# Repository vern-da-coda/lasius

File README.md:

# Lasius Hexapod

---

[Index](README.md) | [Software](software/README.md) | [Hardware](hardware/README.md) | [Docs](docs/README.md) | [Data](data/README.md) | [Scripts](scripts/README.md) |<br>
[Architecture](#folder-architecture) | [Subsystems](#core-subsystems--capabilities) | [Documentation Index](#documentation-index--navigation) | [Quickstart](#quickstart) |

---

<p align="left">

</p>
<p align="left">

</p>

Modular control software, rigid-body physics simulation, 3D Digital Twin, REST/WebSocket teleoperation daemon, and CAD engineering pipeline for an 18-DOF, 6-legged (hexapod) biomimetic walking robot.

**Interactive Web Demo:** [**https://dashboard.lasius.kaemmereit.de/**](https://dashboard.lasius.kaemmereit.de/) – Experience the browser-based 3D Digital Twin and gait engine live.

Lasius combines embedded locomotion control, 3D physics simulation (PyBullet & MuJoCo), Gymnasium Reinforcement Learning, real-time WebGL visualization, physical CAD engineering, and gamepad teleoperation into a single unified monorepo. The physical robot features a dual carbon-fiber sandwich chassis, 18 high-torque metal-gear servos driven by dual PCA9685 PWM controllers, closed-form 3-DOF inverse kinematics, a smooth 50 Hz harmonic cosine walking engine, and an interactive Digital Twin built with Vue 3 and Three.js.

---

## Core Subsystems & Capabilities

### 1. Embedded Locomotion Engine (`software/lasius-core`)
- **50 Hz Harmonic OmniGait Engine:** $C^1$-continuous trajectory generator with smooth cosine stance/swing transitions, $>5\times$ acceleration jerk reduction, and seamless morphing between **Tripod**, **Ripple**, and **Wave** gaits.
- **Analytical 3-DOF Inverse Kinematics:** Closed-form solver computing joint angles $(\theta_{\text{coxa}}, \theta_{\text{femur}}, \theta_{\text{tibia}})$ from foot Cartesian coordinates $(x, y, z)$.
- **Dynamic 6-DOF Body Attitude:** Real-time adjustment of ground clearance ($z \in [-130, -40]\,\text{mm}$), chassis roll, and pitch without altering foot ground contact.
- **REST & WebSocket API:** OpenAPI 3.1 specification serving high-level locomotion orders (`set_velocity`, `set_gait`, `reset_pose`), 25 Hz joint angle telemetry, and 10 Hz system KPIs.

### 2. 3D Physics Digital Twin & Reinforcement Learning (`scripts/sim/`)
- **Physics Simulation (PyBullet & MuJoCo):** 240 Hz rigid-body simulation with Coulomb ground friction ($\mu = 1.2$), accurate joint limits, and stable insect stance with elevated femur and 90° tibia horn offset.
- **Automated FreeCAD $\to$ URDF Pipeline:** `scripts/sim/extract_inertias.py` analytically computes masses and 3D inertia tensors directly from CAD solid models; `scripts/sim/export_urdf.py` generates [`hardware/mechanics/export/urdf/lasius.urdf`](hardware/mechanics/export/urdf/lasius.urdf).
- **Gymnasium Environment (`LasiusGymEnv`):** Standardized RL interface with 66-dimensional observation space (projected gravity vector, linear/angular velocities, joint errors, action history) and 18-dimensional continuous action space (Residual RL).
- **PPO Policy Training:** Stable-Baselines3 training pipeline (`scripts/sim/train_rl.py`) running at $>420\,\text{FPS}$ on laptop CPUs for residual gait adaptation.

### 3. 3D Web Dashboard (`software/lasius-dashboard`)
- **Vue 3 + TypeScript Single-Page App:** Reactive dashboard with Three.js WebGL 3D Digital Twin, 2D orthographic CAD projections, and real-time state telemetry.
- **Leg Control & Calibration:** Interactive joint inspection (`JointCard.vue`) supporting individual servo angle sliders, 0° reference alignment, automated collision sweeps, and live microsecond trim overlay persistence.
- **Ground Coupling:** Dynamic support plane calculation (`fitSupportPlane`) supporting *Ground Locked* (moving floor grid) and *Test Stand* (bench isolation) modes with active foot contact glow indicators.
- **Standalone Client Simulation:** Runs in browser without robot connection via an additive TypeScript kinematics engine ([`dashboard.lasius.kaemmereit.de`](https://dashboard.lasius.kaemmereit.de/)).

### 4. Gamepad Teleoperation (`software/lasius-pilot`)
- **Multi-Controller Support:** Native Linux joystick driver (`/dev/input/js0`) with auto-detecting YAML profiles for **Sony PS5 DualSense**, **Google Stadia**, and **Xbox** controllers.
- **Unified Orchestration (`scripts/sim/sim_pilot.sh`):** Concurrent startup of PyBullet 3D simulation, HTTP Web Dashboard, WebSocket bridge, and `lasius-pilot` teleoperation with graceful single-signal shutdown.

### 5. I2C Sensor Bus & Testbench (`hardware/electronics/`, `scripts/bench/`)
- **Two-Tier I2C & Logic Architecture:** Dual **Controllers** (`PCA9685` `0x40` left, `0x42` right) daisy-chained with the central **Multiplexer** (`PCA9548A` at `0x71`, avoiding `0x70 ALLCALL`), isolated per-leg **Wandler** ADCs (`6× ADS1115 V280` at `0x48` on `CH0–CH5`, verified `SCL`-before-`SDA` pinout and effective 12-bit / `2.0 mV` steps) reading servo potentiometers & Omron D2F-L foot switches (`A3`), plus a central `3.3V / GND` distribution rail tied once to `Star_Ground_Bus`.
- **Automated Diagnostic Tool (`scripts/bench/test_electronics.py`):** Full topology scan, sub-channel switching, and live analog voltage monitor with offline `--mock` mode.

---

## Folder Architecture

The repository is organized into focused subdomains:

```text
lasius/
├── software/            # Monorepo software packages
│   ├── lasius-core/     # Locomotion engine, HAL, Gymnasium environment & REST/WS daemon
│   ├── lasius-dashboard/# Vue 3 + TypeScript + Three.js 3D Digital Twin & browser GUI
│   └── lasius-pilot/    # Gamepad teleoperation client & Linux joystick driver
├── hardware/            # Physical robot engineering
│   ├── mechanics/       # Parametric FreeCAD models, STL/STEP exports & 1:1 drill templates
│   └── electronics/     # Sensor bus topology, WireViz harness diagrams & BOMs
├── docs/                # Architecture specifications, hardware plans & roadmap
├── data/                # Calibration snapshots, benchmarks & telemetry logs
└── scripts/             # Development, simulation, bench diagnostics & deployment tools
```

---

## Documentation Index & Navigation

Direct links to all distributed technical documentation, specifications, hardware plans, and subsystem guides:

### System & Architecture (`docs/`)
- [**`docs/README.md`**](docs/README.md) – Documentation overview and navigation guide
- [**`docs/domain_architecture.md`**](docs/domain_architecture.md) – Comprehensive system & domain architecture specification (6 Domains, C4 map & sequence workflows)
- [**`docs/roadmap.md`**](docs/roadmap.md) – Project roadmap, milestone progress (M1–M6), and backlog
- [**`docs/audio_briefing_domain.md`**](docs/audio_briefing_domain.md) – Audio podcast briefing script covering mechanics, kinematics, and software architecture

### Hardware & Electronics (`docs/hardware/`, `hardware/`)
- [**`docs/hardware/testbench_bringup_status.md`**](docs/hardware/testbench_bringup_status.md) – **Active Focus:** Step-by-step Bring-Up status and handover for TCA9548A & ADS1115 ADCs
- [**`docs/hardware/electronics_testbench_guide.md`**](docs/hardware/electronics_testbench_guide.md) – Technical reference guide, wiring pinouts, 3.3V logic rules, and I2C address conflict protection
- [**`docs/hardware/decisions.md`**](docs/hardware/decisions.md) – Hardware decisions, power architecture (LiPo/UBEC), sensor bus & PETG 3D print specifications
- [**`docs/hardware/closed_loop_plan.md`**](docs/hardware/closed_loop_plan.md) – 18-DOF closed-loop feedback plan, ADS1115 ADC pinout & CircuitPython drivers
- [**`docs/hardware/wiring_plan.md`**](docs/hardware/wiring_plan.md) – Raspberry Pi to PCA9685 I2C daisy chain, logic levels & common ground scheme
- [**`hardware/README.md`**](hardware/README.md) – Hardware overview, dual-plate chassis dimensions, limb lengths & power distribution
- [**`hardware/mechanics/README.md`**](hardware/mechanics/README.md) – FreeCAD parametric models, fabrication exports (STEP, STL, DXF) & SVG drill templates
- [**`hardware/mechanics/STYLE_GUIDE.md`**](hardware/mechanics/STYLE_GUIDE.md) – Mechanical & Hardware Style-Guide (Bionic design DNA, truss standards, DfAM for PETG & COTS interfaces)
- [**`hardware/electronics/wiring/README.md`**](hardware/electronics/wiring/README.md) – WireViz cable harnesses (`.yml`), visual harness diagrams, master color scheme & automated BOMs
- [**`hardware/electronics/TODO.md`**](hardware/electronics/TODO.md) – Electronics bench verification status, master color scheme, `3.3V/GND` rail & wiring backlog

### Teleoperation & Controls (`docs/pilot/`)
- [**`docs/pilot/gamepad_stadia.md`**](docs/pilot/gamepad_stadia.md) – Google Stadia Bluetooth/USB controller profile, button mappings & teleoperation

### Software Subsystems (`software/`)
- [**`software/README.md`**](software/README.md) – Software architecture overview and package guide
- [**`software/TODO.md`**](software/TODO.md) – Biomimetic backlog, Walknet ganglia architecture, and active sprint tasks
- [**`software/lasius-core/README.md`**](software/lasius-core/README.md) – Locomotion engine, 50 Hz harmonic gait, 3-DOF IK, HAL, and REST/WebSocket API
- [**`software/lasius-dashboard/README.md`**](software/lasius-dashboard/README.md) – Vue 3 + TypeScript 3D Digital Twin (Three.js WebGL), 2D projections & control GUI
- [**`software/lasius-pilot/README.md`**](software/lasius-pilot/README.md) – Direct Linux joystick driver (`/dev/input/js0`), radial deadzones & teleoperation streaming

### Data, Benchmarks & Tooling (`data/`, `scripts/`)
- [**`data/README.md`**](data/README.md) – Runtime data index, calibration snapshots & benchmark measurements
- [**`data/bench/README.md`**](data/bench/README.md) – Potentiometer sweep calibration data, linear regression parameters & validation results
- [**`scripts/README.md`**](scripts/README.md) – Complete guide to automation, simulation, testing, diagnostic, and deployment scripts

---

## Quickstart

### 1. Installation & Dependencies

```bash
# Set up Python environment and packages in editable mode:
uv sync --extra dev
# or: pip install -e software/lasius-core -e software/lasius-pilot

# Install frontend dependencies and build dashboard:
cd software/lasius-dashboard && npm install && npm run build && cd ../..
```

### 2. Run Automated Test Suite

```bash
./scripts/dev/run_tests.sh
```
*Executes all 66 automated unit and integration tests across `lasius-core` (HAL, kinematics, gait, GymEnv, orders) and `lasius-pilot`.*

### 3. Interactive 3D Physics Simulation & Gamepad Teleoperation

Launch PyBullet rigid-body physics, the 3D Web Dashboard, and Gamepad teleoperation (PS5 DualSense / Stadia / Xbox) concurrently:

```bash
./scripts/sim/sim_pilot.sh
```

Or start the standalone PyBullet 3D simulation directly:
```bash
python3 scripts/sim/run_simulation.py --gui
```

### 4. Local Simulation Server & Web Digital Twin

```bash
./scripts/dev/dev_sim.sh
```

Open your browser at:
- **3D Dashboard & Control GUI:** `http://127.0.0.1:8000`
- **Interactive OpenAPI Specification:** `http://127.0.0.1:8000/api/v1/openapi.yaml`
- **Telemetry WebSocket:** `ws://127.0.0.1:8765`

### 5. Electronics Testbench Diagnostics

Test I2C connectivity and the TCA9548A / ADS1115 sensor bus:

```bash
# On physical Raspberry Pi:
python3 scripts/bench/test_electronics.py --scan

# Offline dry-run on development workstation:
python3 scripts/bench/test_electronics.py --scan --mock
```

### 6. Deploy to Physical Raspberry Pi 4

```bash
./scripts/deploy/deploy_pi.sh [PI_IP]
```

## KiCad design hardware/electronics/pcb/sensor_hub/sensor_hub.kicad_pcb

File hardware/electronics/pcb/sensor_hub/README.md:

# Lasius Sensor Hub & 3.3V / GND Distribution Carrier Board v2

---

[Project Index](../../../../README.md) | [Electronics Roadmap](../../TODO.md) | [Wiring Plan](../../../../docs/hardware/wiring_plan.md) |<br>
[Wiring Harness Spec](../../WIRING_HARNESS_SPEC.md) | [Chassis Core Assembly](../../../mechanics/models/custom/v2/chassis_core_assembly.FCStd)

---

Dieses KiCad-Projekt umfasst das vollständige Design, den Bestückungsplan und die fertigen Fertigungsdaten (Gerber RS-274X + Excellon Drill) für das zentrale Sensor- und Power-Carrier-Board des **Lasius** Hexapods.

Die Platine sitzt auf den integrierten M2.5-Domen des Zwischenbodens ($Z = 28{,}00\,\text{mm}$) im $24\,\text{mm}$-Spalt zwischen den beiden PCA9685 PWM-Controllern und ist **zu 100 % form- und maßkompatibel zum FreeCAD-Volumenmodell** ([`sensor_hub_board.FCStd`](../../../mechanics/models/custom/v2/parts/chassis/sensor_hub_board.FCStd)).

---

## 1. Board-Spezifikationen

| Parameter | Wert | Beschreibung |
| :--- | :--- | :--- |
| **Abmessungen** | $54{,}0 \times 22{,}0 \times 1{,}60\,\text{mm}$ | Passgenau für den Zwischenboden-Schacht; $R = 2{,}0\,\text{mm}$ Eckenradien. |
| **Lagen** | 2 Lagen (Top + Bottom) | Standard FR4, $35\,\mu\text{m}$ Cu ($1\,\text{oz}$), Matt-Schwarz oder Waldgrün. |
| **Befestigung** | 2× M2.5 Bohrungen | $\varnothing 2{,}7\,\text{mm}$ im Abstand von $26{,}0\,\text{mm}$ ($X = 0{,}0, Y = \pm 13{,}0\,\text{mm}$). |
| **Multiplexer-Sockel** | 2× 12-Pin Buchsenleiste | $2{,}54\,\text{mm}$ Raster, $17{,}54\,\text{mm}$ Reihenabstand für TCA9548A / PW548A. |
| **Adresse** | **`0x71`** (Hardware-Fixed) | `A0` fest auf `3,3 V` verdrahtet; `A1` und `A2` auf `GND`. |
| **Bein-Steckplätze** | 6× 4-Pin Stiftleisten | $2{,}54\,\text{mm}$ THT (oder JST-XH), straight $1:1$ Pinout passend zu V280 ADC. |

---

## 2. Pinbelegung der 4-Pin Bein-Steckplätze

Das Pinout ist **exakt 1:1 identisch zur Reihenfolge auf den ADS1115 (`V280`) Platinen im Femur**, sodass handelsübliche 4-adrige Flachbandleitungen ohne gekreuzte Adern verwendet werden können:

| Pin | Signal | Drahtfarbe ([Master-Farbschema](../../WIRING_HARNESS_SPEC.md)) | Beschreibung |
| :---: | :--- | :--- | :--- |
| **1** | **`3,3 V`** | **Rot** | Geregelte Logikspannung vom Pi 4 (Pin 1) |
| **2** | **`GND`** | **Schwarz** | Star-GND Referenzmasse |
| **3** | **`SCx`** | **Gelb** | Multiplexer I²C-Takt (`SCL`) für Kanal $x$ |
| **4** | **`SDx`** | **Kanal-Farbe** | Multiplexer I²C-Daten (`SDA`) für Kanal $x$ |

### Kanal-Zuordnung & Kabelfarben:
* **Bank 1 ($+Y$, zeigt nach links):**
  * `J_LF` (CH0): Blau (`SD0`) + Gelb (`SC0`) $\rightarrow$ Bein Vorne Links (LF)
  * `J_LM` (CH1): Grün (`SD1`) + Gelb (`SC1`) $\rightarrow$ Bein Mitte Links (LM)
  * `J_LR` (CH2): Violett (`SD2`) + Gelb (`SC2`) $\rightarrow$ Bein Hinten Links (LR)
  * `J_RPI` (Main Bus): Blau (`SDA`) + Gelb (`SCL`) $\rightarrow$ Haupteingang vom Raspberry Pi
  * `J_PCA_L`: 2-Pin Versorgungsabgang (`3,3V / GND`) zum linken PCA9685-Controller
* **Bank 2 ($-Y$, zeigt nach rechts):**
  * `J_FR` (CH3): Orange (`SD3`) + Gelb (`SC3`) $\rightarrow$ Bein Vorne Rechts (FR)
  * `J_RM` (CH4): Weiß (`SD4`) + Gelb (`SC4`) $\rightarrow$ Bein Mitte Rechts (RM)
  * `J_RR` (CH5): Grau (`SD5`) + Gelb (`SC5`) $\rightarrow$ Bein Hinten Rechts (RR)
  * `J_AUX`: 4-Pin Erweiterung für CH6 (INA228 Stromsensor, Braun) und CH7 (ToF)
  * `J_PCA_R`: 2-Pin Versorgungsabgang (`3,3V / GND`) zum rechten PCA9685-Controller

---

## 3. Stückliste (Bill of Materials / BOM)

| Ref | Bauteil | Gehäuse / Raster | Spezifikation / Notiz |
| :--- | :--- | :--- | :--- |
| **U1** | TCA9548A / PW548A | Breakout-Modul | 8-Kanal I²C Multiplexer Modul (violett) |
| **J_TCA_L, J_TCA_R** | 2× 12-Pin Buchsenleiste | $2{,}54\,\text{mm}$ THT, 1-reihig | Bauhöhe $4{,}0\dots 8{,}5\,\text{mm}$ zum werkzeuglosen Stecken |
| **J_LF, J_LM, J_LR** | 3× 4-Pin Stiftleiste | $2{,}54\,\text{mm}$ THT (oder JST-XH) | Linke Beinbank ($+Y$) |
| **J_FR, J_RM, J_RR** | 3× 4-Pin Stiftleiste | $2{,}54\,\text{mm}$ THT (oder JST-XH) | Rechte Beinbank ($-Y$) |
| **J_RPI, J_AUX** | 2× 4-Pin Stiftleiste | $2{,}54\,\text{mm}$ THT | Pi Haupteingang & Sensor-Erweiterung |
| **J_PCA_L, J_PCA_R** | 2× 2-Pin Stiftleiste | $2{,}54\,\text{mm}$ THT | Controller Logik-Versorgung |
| **C1** | $10\,\mu\text{F}$ Elko / Tantal | Radial $D = 5{,}0\,\text{mm}$, RM $2{,}5\,\text{mm}$ | $\ge 6{,}3\,\text{V}$ Entkopplung auf der 3,3V-Schiene |
| **C2** | $100\,\text{nF}$ Keramikkondensator | Disc / MLCC RM $2{,}5\,\text{mm}$ | Hochfrequenz-Entstörung nah am Multiplexer |
| **H1, H2** | 2× M2.5 Schrauben | Zylinderkopf / Linsenkopf | Befestigung in den Monocoque-Domen ($L = 6\dots 8\,\text{mm}$) |

---

## 4. Fertigung & Bestellung (Ready-to-Order)

Die produktionsfertigen Gerber-Daten liegen gepackt bereit unter:  
**[`sensor_hub_gerbers.zip`](sensor_hub_gerbers.zip)**

### Bestellung bei JLCPCB:
1. `sensor_hub_gerbers.zip` per Drag & Drop auf [jlcpcb.com](https://jlcpcb.com) hochladen.
2. Abmessungen werden automatisch erkannt: **$54 \times 22\,\text{mm}$**, 2 Lagen.
3. PCB Color nach Wunsch wählen (Empfehlung: **Matte Black** passend zum Anthrazit PA-CF Chassis).
4. Fertigungskosten: ca. **2 $ für 5 Stück**.

### Bestellung bei AISLER:
1. `sensor_hub_gerbers.zip` (oder direkt die `.kicad_pcb`-Datei) auf [aisler.net](https://aisler.net) hochladen.
2. „Beautiful PCBs“ auswählen (Lieferzeit: **3–4 Werktage** aus Deutschland/Niederlande).

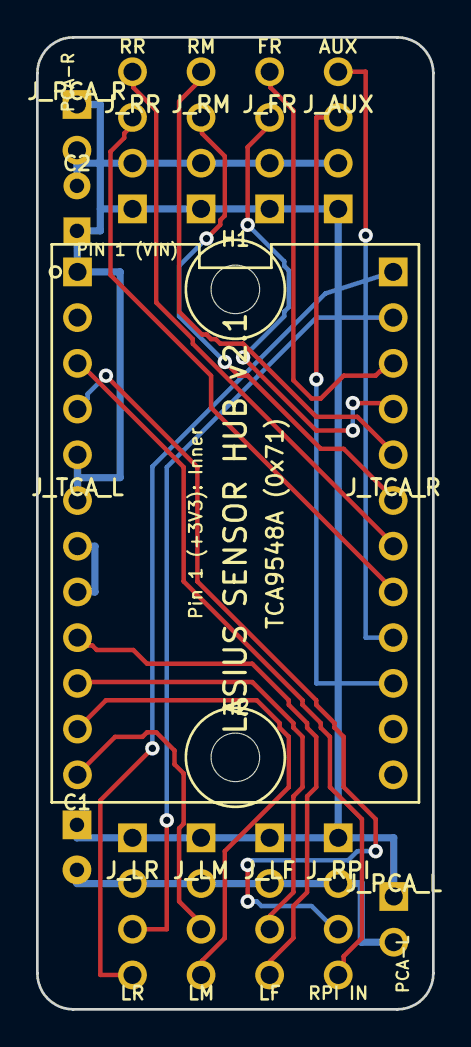
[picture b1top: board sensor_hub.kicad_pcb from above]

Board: 2 copper layers, 22.0 x 54.0 mm, 16 parts (0 on the bottom side), 18 nets.

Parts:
C1: 10uF; CP_Radial_D5.0mm_P2.50mm
C2: 100nF; C_Disc_D4.7mm_W2.6mm_P2.50mm
H1, H2: MountingHole_M2.5; MountingHole_2.7mm_M2.5
J_AUX: AUX_Sensors_CH6; PinHeader_1x04_P2.54mm_Vertical
J_FR: Right_Front_CH3; PinHeader_1x04_P2.54mm_Vertical
J_LF: Left_Front_CH0; PinHeader_1x04_P2.54mm_Vertical
J_LM: Left_Middle_CH1; PinHeader_1x04_P2.54mm_Vertical
J_LR: Left_Rear_CH2; PinHeader_1x04_P2.54mm_Vertical
J_PCA_L: PCA9685_Left_PWR; PinHeader_1x02_P2.54mm_Vertical
J_PCA_R: PCA9685_Right_PWR; PinHeader_1x02_P2.54mm_Vertical
J_RM: Right_Middle_CH4; PinHeader_1x04_P2.54mm_Vertical
J_RPI: Pi_Main_I2C_In; PinHeader_1x04_P2.54mm_Vertical
J_RR: Right_Rear_CH5; PinHeader_1x04_P2.54mm_Vertical
J_TCA_L: TCA9548A_Socket_Left; PinHeader_1x12_P2.54mm_Vertical
J_TCA_R: TCA9548A_Socket_Right; PinHeader_1x12_P2.54mm_Vertical

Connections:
+3V3: C1.1, C2.1, J_AUX.1, J_FR.1, J_LF.1, J_LM.1, J_LR.1, J_PCA_L.1, J_PCA_R.1, J_RM.1, J_RPI.1, J_RR.1, J_TCA_L.1, J_TCA_L.5, J_TCA_L.6
GND: C1.2, C2.2, J_AUX.2, J_FR.2, J_LF.2, J_LM.2, J_LR.2, J_PCA_L.2, J_PCA_R.2, J_RM.2, J_RPI.2, J_RR.2, J_TCA_L.2, J_TCA_L.7, J_TCA_L.8
SCL0: J_LF.3, J_TCA_L.10
SCL1: J_LM.3, J_TCA_L.12
SCL2: J_LR.3, J_TCA_R.2
SCL3: J_FR.3, J_TCA_R.4
SCL4: J_RM.3, J_TCA_R.6
SCL5: J_RR.3, J_TCA_R.8
SCL6: J_AUX.3, J_TCA_R.10
SCL_MAIN: J_RPI.3, J_TCA_L.4
SDA0: J_LF.4, J_TCA_L.9
SDA1: J_LM.4, J_TCA_L.11
SDA2: J_LR.4, J_TCA_R.1
SDA3: J_FR.4, J_TCA_R.3
SDA4: J_RM.4, J_TCA_R.5
SDA5: J_RR.4, J_TCA_R.7
SDA6: J_AUX.4, J_TCA_R.9
SDA_MAIN: J_RPI.4, J_TCA_L.3
